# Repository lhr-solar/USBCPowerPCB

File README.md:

# USBCPowerPCB
Author: Ishan Deshpande

The purpose of this board is to be able to use a USB Type-C laptop charger to run one LV system (such as BPS or Controls). The dongle will act as a breakout; negotiating the power delivery at a fixed voltage with the laptop charger and delivering as much current as needed at a stable voltage of 12V/5V.

Currently under active development. Please reference the [USB-C PD Dongle Design Document](https://cloud.wikis.utexas.edu/wiki/spaces/LHRSOLAR/pages/28287742/2024+-+2026+USB-C+PD+Dongle+Design+Document) for more information.

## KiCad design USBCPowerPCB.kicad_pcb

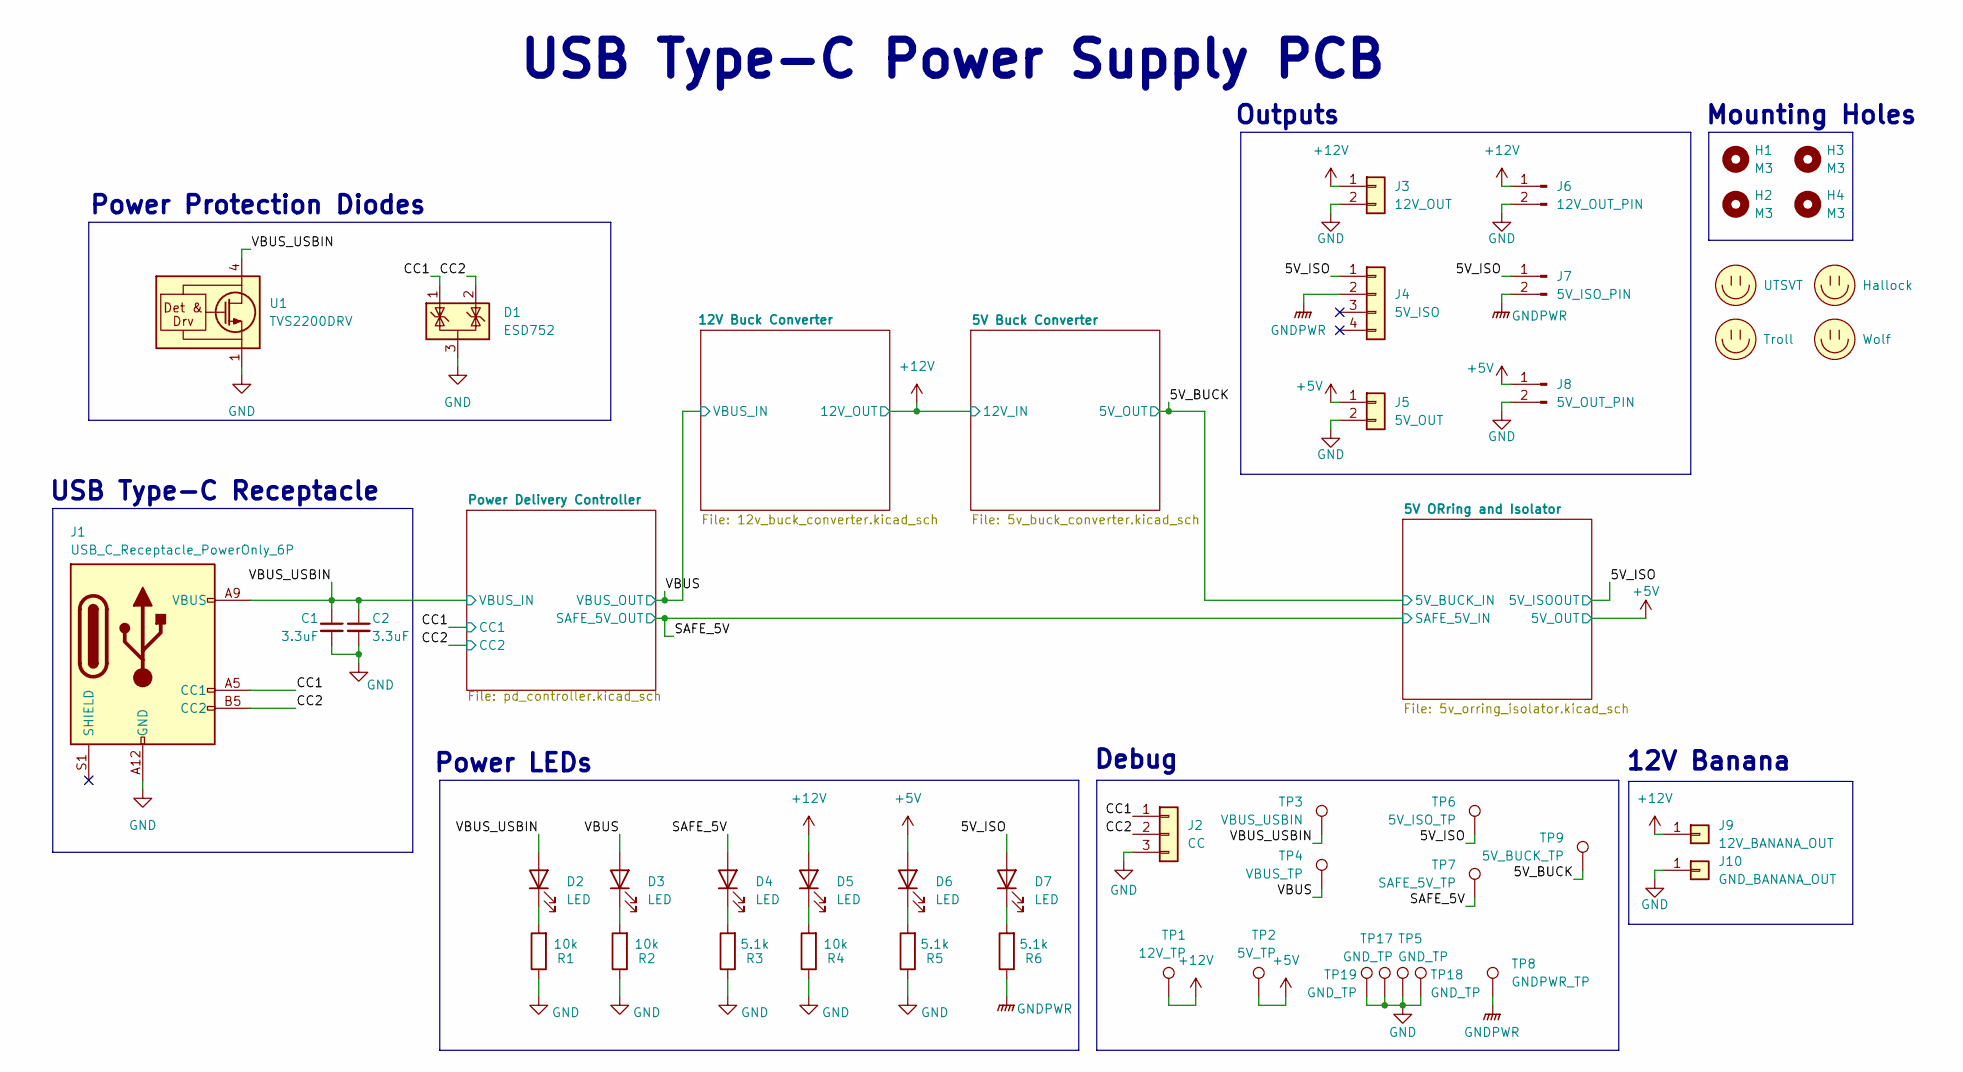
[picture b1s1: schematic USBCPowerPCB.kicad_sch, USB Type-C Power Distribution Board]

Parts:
C1, C2: 3.3uF; C_0805_2012Metric
D1: ESD752; SOT-23; Mouser Part Number ESD752DBZR
D2, D3, D4, D5, D6, D7: LED; LED_0805_2012Metric
H1, H2, H3, H4: M3; MountingHole_3.2mm_M3
J1: USB_C_Receptacle_PowerOnly_6P; TYPEC31M17
J2: CC; PinHeader_1x03_P2.54mm_Vertical
J3: 12V_OUT; Molex_MicroFit3.0_1x2xP3.00mm_PolarizingPeg_Vertical
J4: 5V_ISO; Molex_MicroFit3.0_1x4xP3.00mm_PolarizingPeg_Vertical
J5: 5V_OUT; Molex_MicroFit3.0_1x2xP3.00mm_PolarizingPeg_Vertical
J6: 12V_OUT_PIN; PinHeader_1x02_P2.54mm_Vertical
J7: 5V_ISO_PIN; PinHeader_1x02_P2.54mm_Vertical
J8: 5V_OUT_PIN; PinHeader_1x02_P2.54mm_Vertical
J9: 12V_BANANA_OUT; Banana_Jack_Horizontal
J10: GND_BANANA_OUT; Banana_Jack_Horizontal
LOGO1: UTSVT; UTSVT_Logo_Symbol
LOGO2: Hallock; Hallock_Image_Tiny
LOGO3: Troll; troll
LOGO4: Wolf; wolf_front
R1, R2, R4: 10k; R_0805_2012Metric
R3, R5, R6: 5.1k; R_0805_2012Metric
TP1: 12V_TP; TestPoint_Plated_Hole_D2.0mm
TP2: 5V_TP; TestPoint_Plated_Hole_D2.0mm
TP3: VBUS_USBIN; TestPoint_Plated_Hole_D2.0mm
TP4: VBUS_TP; TestPoint_Plated_Hole_D2.0mm
TP5, TP17, TP18: GND_TP; TestPoint_THTPad_1.0x1.0mm_Drill0.5mm
TP6: 5V_ISO_TP; TestPoint_Plated_Hole_D2.0mm
TP7: SAFE_5V_TP; TestPoint_Plated_Hole_D2.0mm
TP8: GNDPWR_TP; TestPoint_Plated_Hole_D2.0mm
TP9: 5V_BUCK_TP; TestPoint_Plated_Hole_D2.0mm
TP19: GND_TP; TestPoint_Plated_Hole_D2.0mm
U1: TVS2200DRV; WSON-6-1EP_2x2mm_P0.65mm_EP1x1.6mm

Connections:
+5V: D6.2 (A), J5.1, J8.1, TP2.1; also elsewhere on the board
+12V: D5.2 (A), J3.1, J6.1, J9.1, TP1.1; also elsewhere on the board
/5V_BUCK: TP9.1; also elsewhere on the board
/5V_ISO: D7.2 (A), J4.1, J7.1, TP6.1; also elsewhere on the board
/CC1: D1.1 (K), J1.A5 (CC1), J2.1; also elsewhere on the board
/CC2: D1.2 (K), J1.B5 (CC2), J2.2; also elsewhere on the board
/SAFE_5V: D4.2 (A), TP7.1; also elsewhere on the board
/VBUS: D3.2 (A), TP4.1; also elsewhere on the board
/VBUS_USBIN: C1.1, C2.1, D2.2 (A), J1.A4 (VBUS), J1.A9 (VBUS), J1.B9 (VBUS), TP3.1, U1.4 (IN), U1.5 (IN), U1.6 (IN); also elsewhere on the board
GND: C1.2, C2.2, D1.3 (A), J1.A1 (GND), J1.A12 (GND), J1.B12 (GND), J2.3, J3.2, J5.2, J6.2, J8.2, J10.1, R1.1, R2.1, R3.1, R4.1, R5.1, TP5.1, TP17.1, TP18.1, TP19.1, U1.1 (GND), U1.2 (GND), U1.3 (GND), U1.7 (GND); also elsewhere on the board
GNDPWR: J4.2, J7.2, R6.1, TP8.1; also elsewhere on the board
unnamed: D2.1 (K), R1.2
unnamed: D3.1 (K), R2.2
unnamed: D4.1 (K), R3.2
unnamed: D5.1 (K), R4.2
unnamed: D6.1 (K), R5.2
unnamed: D7.1 (K), R6.2

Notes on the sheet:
Outputs
Mounting Holes
Debug
Power LEDs
USB Type-C Power Supply PCB
USB Type-C Receptacle
12V Banana
Power Protection Diodes

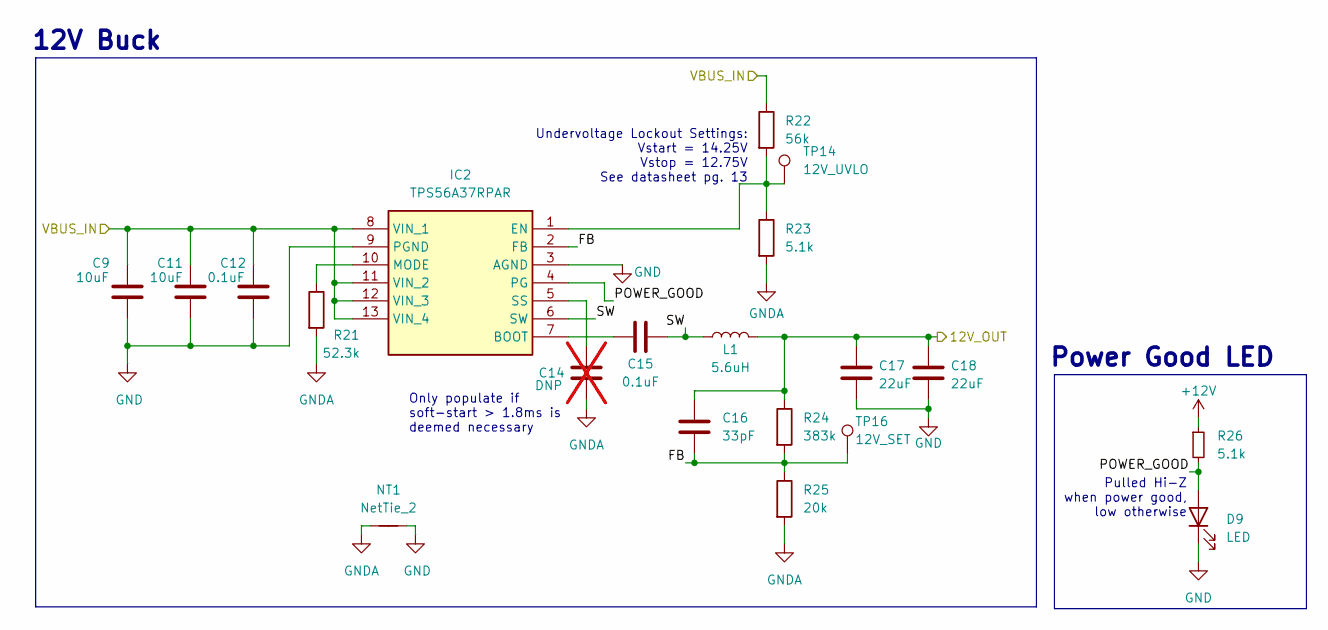
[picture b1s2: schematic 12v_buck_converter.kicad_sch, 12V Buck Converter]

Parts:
C9, C11: 10uF; C_0805_2012Metric; Mouser Part Number GRM21BR61H106KE43L
C12, C15: 0.1uF; C_0805_2012Metric; Mouser Part Number C0805C104M5RACTU
C14: DNP; C_0805_2012Metric; not fitted
C16: 33pF; C_0805_2012Metric; Mouser Part Number C0805C330K5RACTU
C17, C18: 22uF; C_0805_2012Metric; Mouser Part Number C2012X5R1V226M125AC
D9: LED; LED_0805_2012Metric; Mouser Part Number 604-APTD2012LCGCK
IC2: TPS56A37RPAR; Mouser Part Number 595-TPS56A37RPAR
L1: 5.6uH; L_Bourns_SRP1038C_10.0x10.0mm; Mouser Part Number SRP1038CC-5R6M
NT1: NetTie_2; NetTie-2_SMD_Pad2.0mm
R21: 52.3k; R_0805_2012Metric; Mouser Part Number CRCW080552K3FKEAC
R22: 56k; R_0805_2012Metric; Mouser Part Number CRCW080556K0FKEAC
R23, R26: 5.1k; R_0805_2012Metric; Mouser Part Number CRCW08055K10FKEAC
R24: 383k; R_0805_2012Metric; Mouser Part Number CRCW0805383KFKEAC
R25: 20k; R_0805_2012Metric; Mouser Part Number CRCW080520K0FKEAC
TP14: 12V_UVLO; TestPoint_THTPad_1.0x1.0mm_Drill0.5mm
TP16: 12V_SET; TestPoint_THTPad_1.0x1.0mm_Drill0.5mm

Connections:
+12V: C16.1, C17.1, C18.1, L1.2, R24.1, R26.1; also elsewhere on the board
/12V Buck Converter/FB: C16.2, IC2.2 (FB), R24.2, R25.1, TP16.1
/12V Buck Converter/POWER_GOOD: D9.2 (A), IC2.4 (PG), R26.2
/12V Buck Converter/SW: C15.2, IC2.6 (SW), L1.1
/VBUS: C9.1, C11.1, C12.1, IC2.8 (VIN_1), IC2.11 (VIN_2), IC2.12 (VIN_3), IC2.13 (VIN_4), R22.1; also elsewhere on the board
GND: C9.2, C11.2, C12.2, C17.2, C18.2, D9.1 (K), IC2.3 (AGND), IC2.9 (PGND), NT1.2; also elsewhere on the board
GNDA: C14.2, NT1.1, R21.2, R23.2, R25.2
unnamed: C15.1, IC2.7 (BOOT)
unnamed: IC2.1 (EN), R22.2, R23.1, TP14.1
unnamed: IC2.10 (MODE), R21.1
unnamed: C14.1, IC2.5 (SS)

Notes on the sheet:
Only populate if soft-start > 1.8ms is deemed necessary
Undervoltage Lockout Settings: Vstart = 14.25V Vstop = 12.75V See datasheet pg. 13
Pulled Hi-Z when power good, low otherwise
Power Good LED
12V Buck

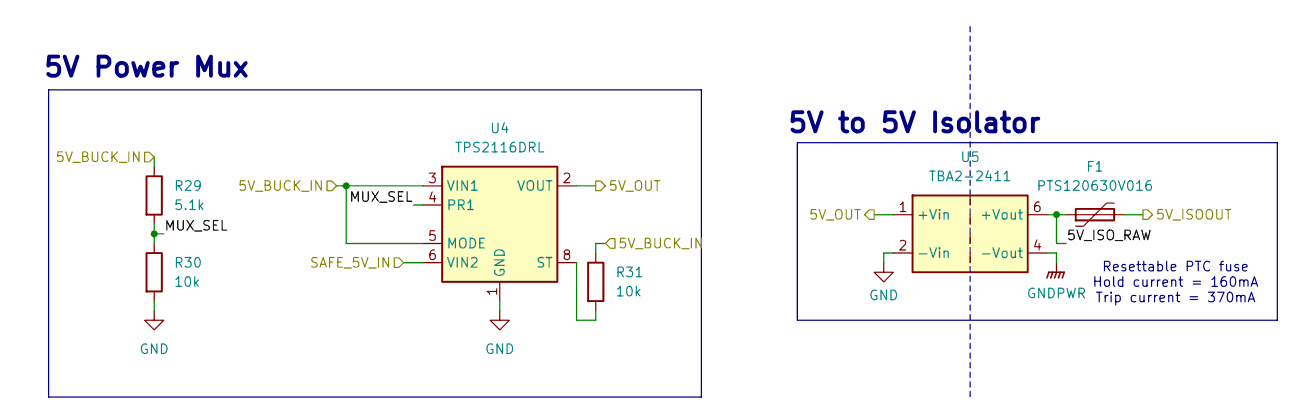
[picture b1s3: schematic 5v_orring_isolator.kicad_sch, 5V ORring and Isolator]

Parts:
F1: PTS120630V016; Fuse_1206_3216Metric
R29: 5.1k; R_0805_2012Metric
R30, R31: 10k; R_0805_2012Metric
U4: TPS2116DRL; SOT-583-8
U5: TBA2-2411; Converter_DCDC_TRACO_TBA2-xxxx_Single_THT

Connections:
+5V: U4.2 (VOUT), U4.7 (VOUT), U5.1 (+Vin); also elsewhere on the board
/5V ORring and Isolator/5V_ISO_RAW: F1.1, U5.6 (+Vout)
/5V ORring and Isolator/MUX_SEL: R29.2, R30.1, U4.4 (PR1)
/5V_BUCK: R29.1, R31.1, U4.3 (VIN1), U4.5 (MODE); also elsewhere on the board
/5V_ISO: F1.2; also elsewhere on the board
/SAFE_5V: U4.6 (VIN2); also elsewhere on the board
GND: R30.2, U4.1 (GND), U5.2 (-Vin); also elsewhere on the board
GNDPWR: U5.4 (-Vout); also elsewhere on the board
unnamed: R31.2, U4.8 (ST)

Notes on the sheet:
5V Power Mux
Resettable PTC fuse Hold current = 160mA Trip current = 370mA
5V to 5V Isolator

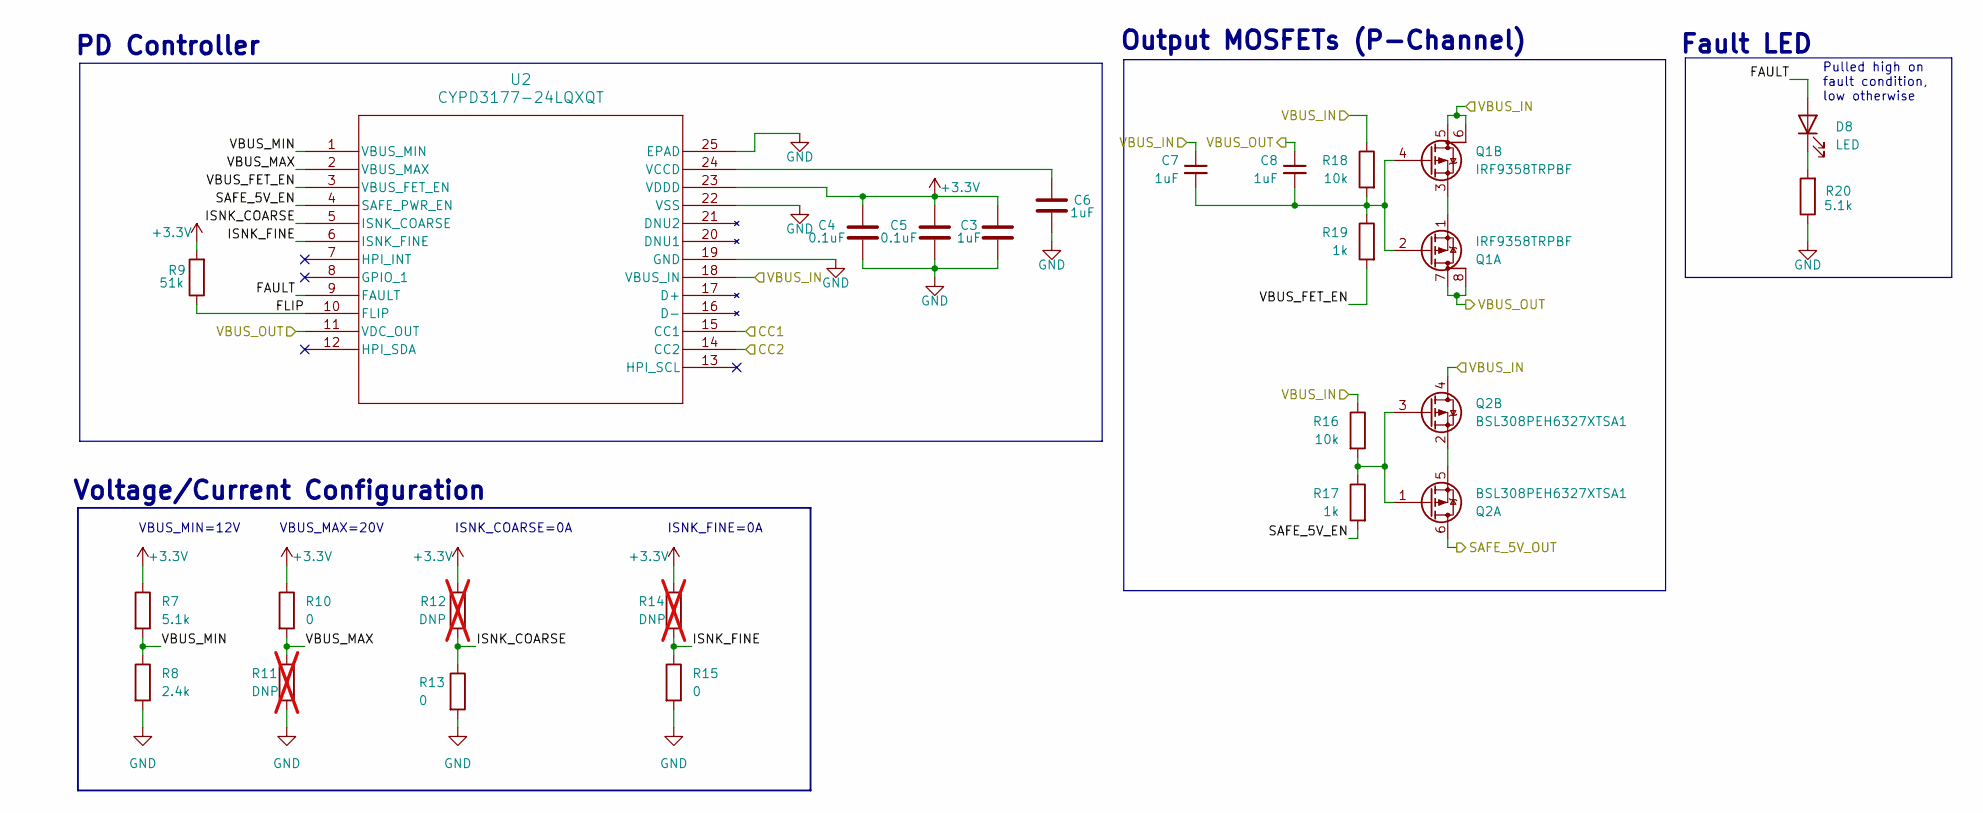
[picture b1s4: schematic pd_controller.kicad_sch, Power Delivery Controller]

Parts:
C3, C6, C7, C8: 1uF; C_0805_2012Metric; Mouser Part Number C0805C105K5PACTU
C4, C5: 0.1uF; C_0805_2012Metric; Mouser Part Number C0805C104M5RACTU
D8: LED; LED_0805_2012Metric; Mouser Part Number 604-APTD2012LCGCK
Q1: IRF9358TRPBF; SO-8_3.9x4.9mm_P1.27mm; Mouser Part Number IRF9358TRPBF
Q2: BSL308PEH6327XTSA1; SOT-23-6; Mouser Part Number BSL308PEH6327XTSA1
R7, R20: 5.1k; R_0805_2012Metric; Mouser Part Number CRCW08055K10FKEAC
R8: 2.4k; R_0805_2012Metric; Mouser Part Number CRCW08052K40FKEAC
R9: 51k; R_0805_2012Metric; Mouser Part Number CRCW080551K0FKEAC
R10, R13, R15: 0; R_0805_2012Metric
R11, R12, R14: DNP; R_0805_2012Metric; not fitted
R16, R18: 10k; R_0805_2012Metric; Mouser Part Number CRCW080510K0FKEAC
R17, R19: 1k; R_0805_2012Metric; Mouser Part Number CRCW08051K00FKEAC
U2: CYPD3177-24LQXQT; CYPD3177-24LQXQT_CYP; Mouser Part Number 727-CYPD3177-24LQXQT

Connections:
+3.3V: C3.2, C4.2, C5.2, R7.1, R9.2, R10.1, R12.1, R14.1, U2.23 (VDDD)
/CC1: U2.15 (CC1); also elsewhere on the board
/CC2: U2.14 (CC2); also elsewhere on the board
/Power Delivery Controller/FAULT: D8.2 (A), U2.9 (FAULT)
/Power Delivery Controller/FLIP: R9.1, U2.10 (FLIP)
/Power Delivery Controller/ISNK_COARSE: R12.2, R13.1, U2.5 (ISNK_COARSE)
/Power Delivery Controller/ISNK_FINE: R14.2, R15.1, U2.6 (ISNK_FINE)
/Power Delivery Controller/SAFE_5V_EN: R17.2, U2.4 (SAFE_PWR_EN)
/Power Delivery Controller/VBUS_FET_EN: R19.2, U2.3 (VBUS_FET_EN)
/Power Delivery Controller/VBUS_MAX: R10.2, R11.1, U2.2 (VBUS_MAX)
/Power Delivery Controller/VBUS_MIN: R7.2, R8.1, U2.1 (VBUS_MIN)
/SAFE_5V: Q2.6 (D); also elsewhere on the board
/VBUS: C8.1, Q1.7 (D), Q1.8 (D), U2.11 (VDC_OUT); also elsewhere on the board
/VBUS_USBIN: C7.1, Q1.5 (D), Q1.6 (D), Q2.4 (D), R16.1, R18.1, U2.18 (VBUS_IN); also elsewhere on the board
GND: C3.1, C4.1, C5.1, C6.1, R8.2, R11.2, R13.2, R15.2, R20.1, U2.19 (GND), U2.22 (VSS), U2.25 (EPAD); also elsewhere on the board
unnamed: D8.1 (K), R20.2
unnamed: C7.2, C8.2, Q1.2 (G), Q1.4 (G), R18.2, R19.1
unnamed: Q1.1 (S), Q1.3 (S)
unnamed: Q2.1 (G), Q2.3 (G), R16.2, R17.1
unnamed: Q2.2 (S), Q2.5 (S)
unnamed: C6.2, U2.24 (VCCD)

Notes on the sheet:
VBUS_MAX=20V
Fault LED
Voltage/Current Configuration
Pulled high on fault condition, low otherwise
PD Controller
ISNK_COARSE=0A
Output MOSFETs (P-Channel)
ISNK_FINE=0A
VBUS_MIN=12V

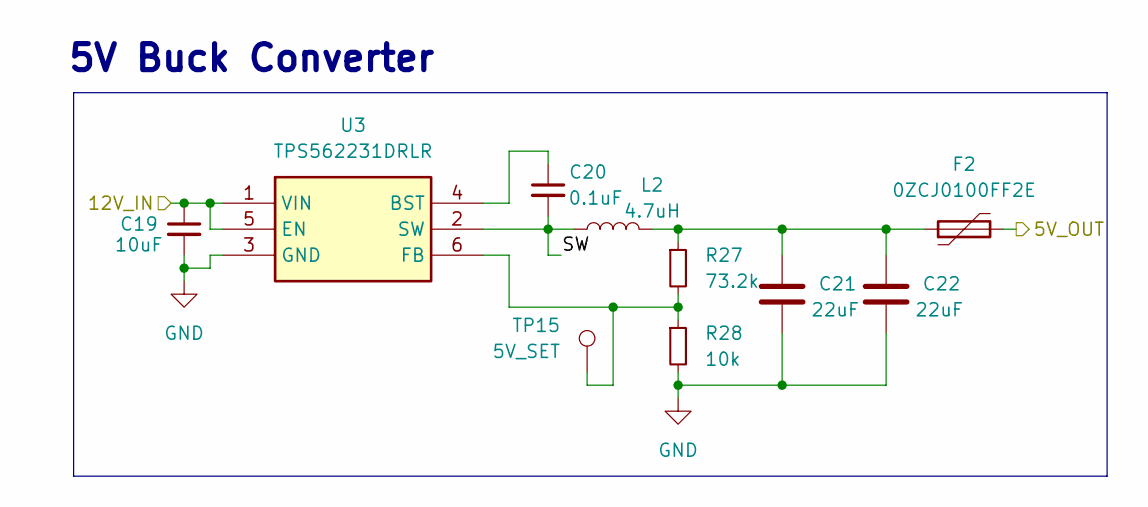
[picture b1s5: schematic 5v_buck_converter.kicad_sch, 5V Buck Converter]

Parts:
C19: 10uF; C_0805_2012Metric
C20: 0.1uF; C_0805_2012Metric
C21, C22: 22uF; C_0805_2012Metric
F2: 0ZCJ0100FF2E; Fuse_1206_3216Metric
L2: 4.7uH; INDPM5452X300N
R27: 73.2k; R_0805_2012Metric
R28: 10k; R_0805_2012Metric
TP15: 5V_SET; TestPoint_THTPad_1.0x1.0mm_Drill0.5mm
U3: TPS562231DRLR; SOT-563

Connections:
+12V: C19.1, U3.1 (VIN), U3.5 (EN); also elsewhere on the board
/5V Buck Converter/SW: C20.2, L2.1, U3.2 (SW)
/5V_BUCK: F2.2; also elsewhere on the board
GND: C19.2, C21.2, C22.2, R28.2, U3.3 (GND); also elsewhere on the board
unnamed: C21.1, C22.1, F2.1, L2.2, R27.1
unnamed: C20.1, U3.4 (BST)
unnamed: R27.2, R28.1, TP15.1, U3.6 (FB)

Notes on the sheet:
5V Buck Converter

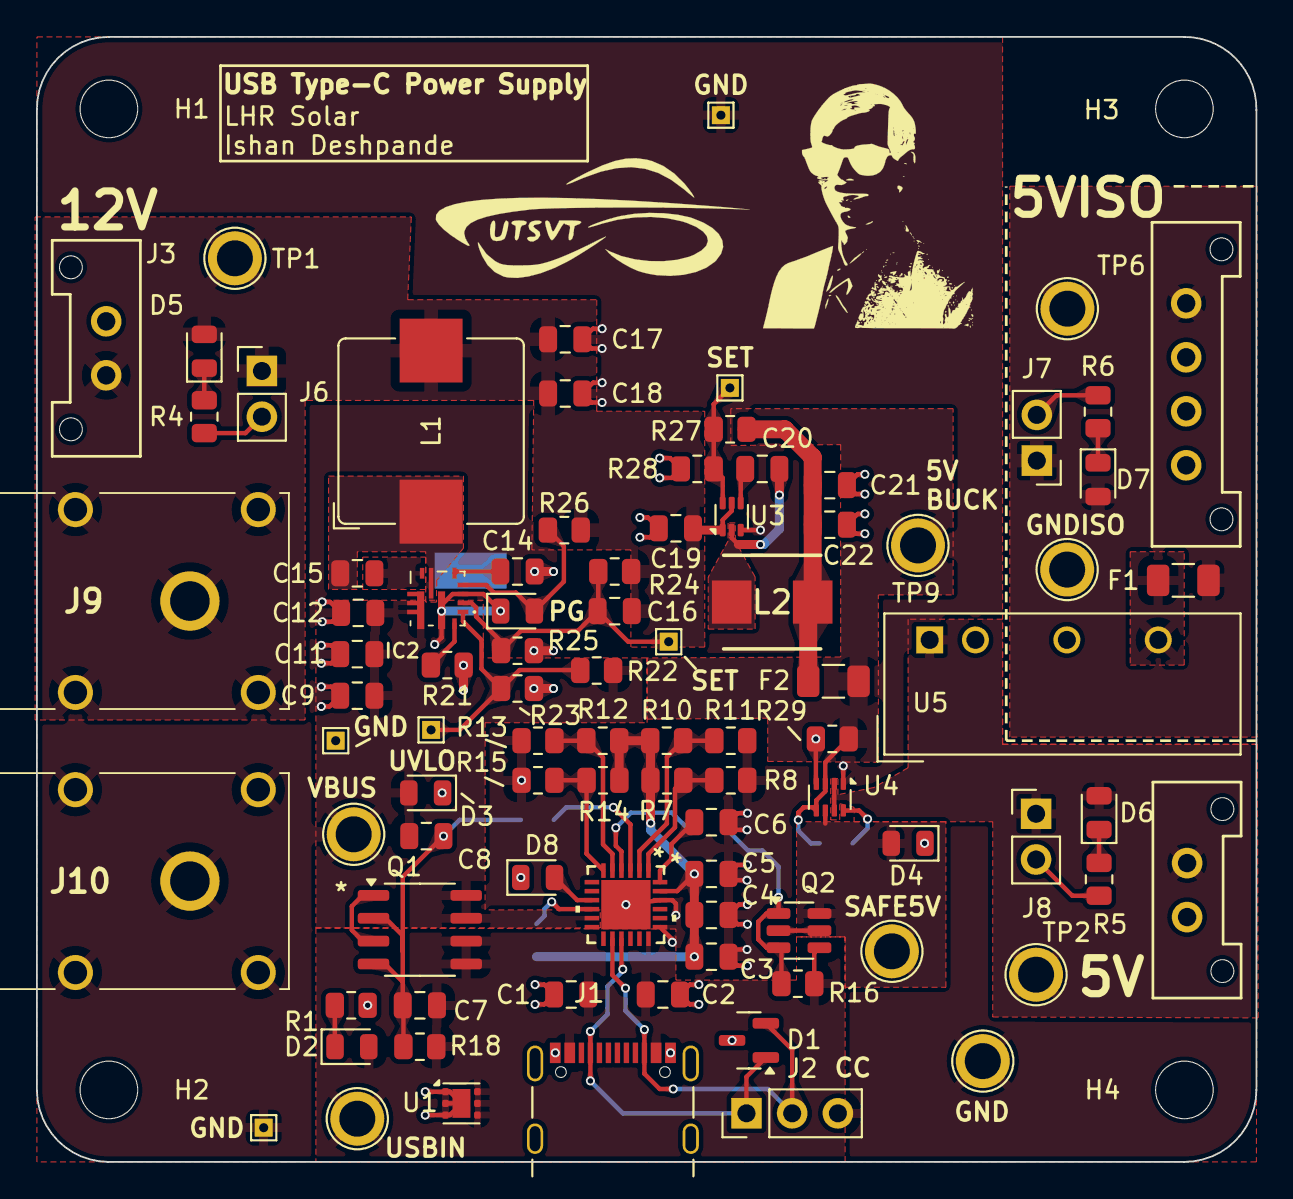
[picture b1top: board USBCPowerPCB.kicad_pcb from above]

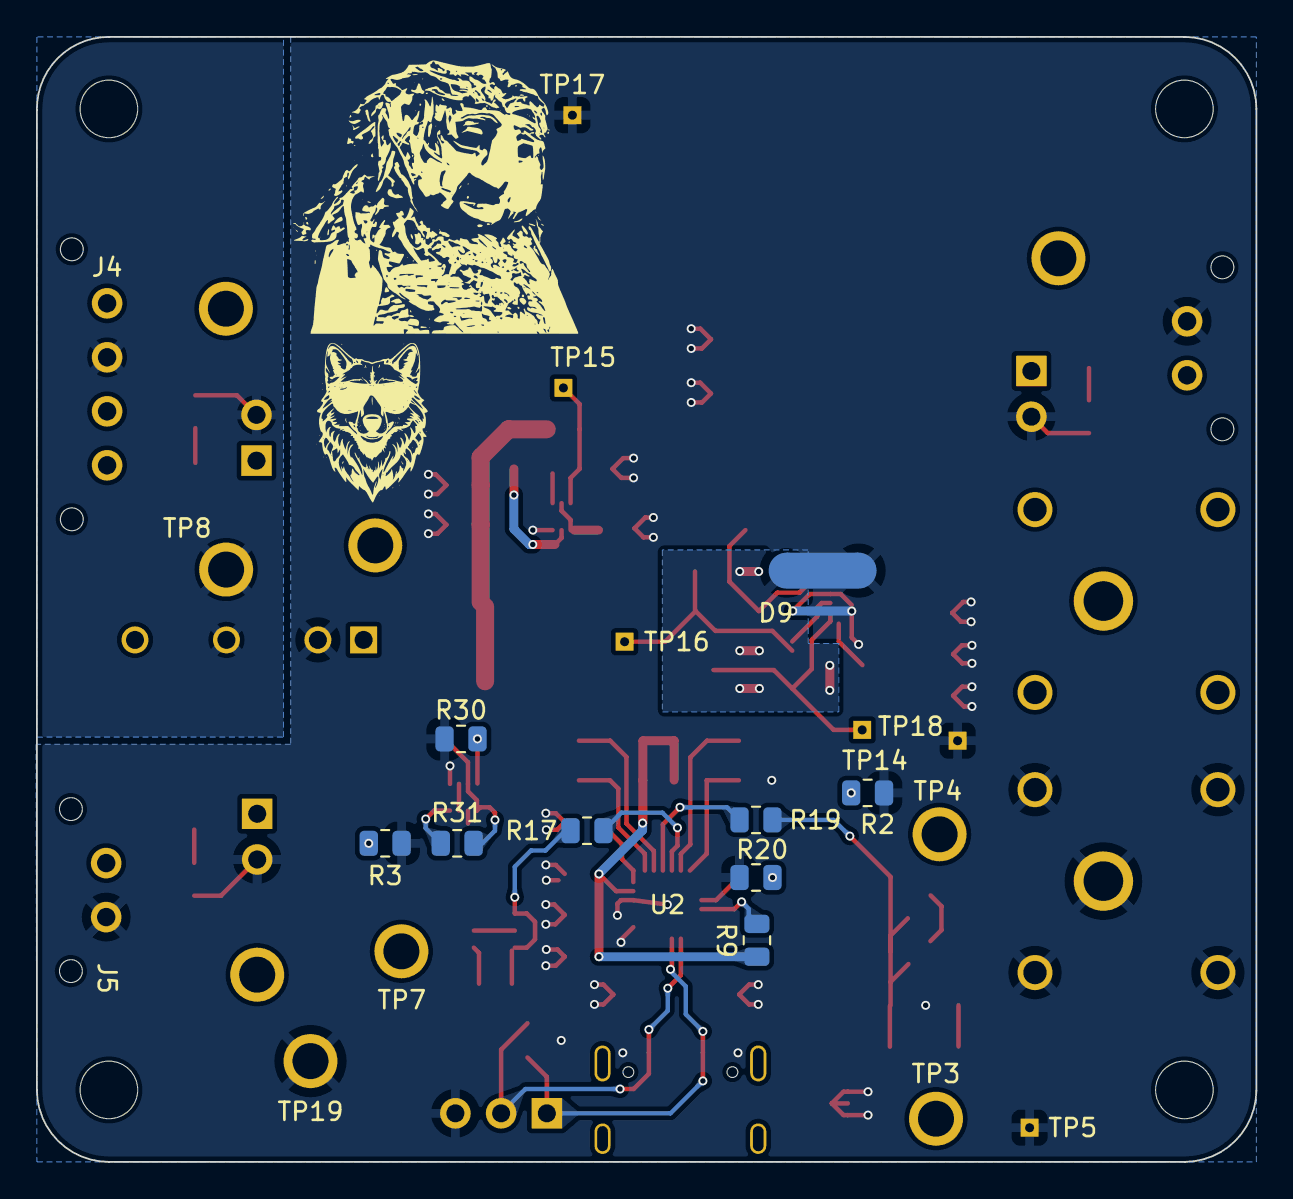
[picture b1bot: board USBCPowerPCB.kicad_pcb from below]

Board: 2 copper layers, 67.8 x 62.5 mm, 106 parts (11 on the bottom side), 47 nets.

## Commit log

2024-05-21 rename, add submodule
2024-06-02 first draft of USBC controller and 12V buck converter schematics
2024-06-02 readme
2024-06-02 added gitignore
2024-06-23 Finished 5V buck converter schematic
2024-06-23 added power good LED indicators
2024-06-23 change current protection to current monitoring
2024-07-27 moving laptops
2024-08-14 initial draft w/ current sense for 5V
2024-08-14 accidentally flipped current sense; also routed high level schematic
2024-08-14 finished first draft
2024-08-14 changed to 1-channel chip for current sense & fixed ERC
2024-08-14 added proper current limiting resistors for 2mA on seven seg
2024-08-15 updated with some new footprints (have yet to finish footprint assignment; also need to switch out inductor for 5V buck)
2024-08-29 add calcs for TPS56A37
2024-08-30 changed 5v buck to TPS56A37
2024-08-31 changed buck calcs for 5v buck
2024-08-31 almost done w/ schematic, just need to finish footprint assignment (make sure buck converter components are correctly chosen and there aren't caps that need to be different and stuff)
2024-08-31 cleaned up schematic, added power LEDs and testpoints
2024-09-01 finished footprint assignment
2024-09-01 added protection diodes
2024-09-02 changed resistor values on infineon chip output mosfets to match EZ PD BCR datasheet better
2024-09-02 removed parallel resistors
2024-09-07 address review changes, add more output protections
2024-09-07 footprint assignment again
2024-09-14 finished addressing review comments & organized bom with p/ns for everything
2024-09-14 added banana jacks for input/output to 12v buck, for isolated 12v buck testing. also filled in more part numbers for connectors.
2024-09-15 intermediate progress push before addressing Champers' and Lakshay's review comments
2024-09-16 Addressed most of the review comments, fixed power protection, added bigger caps & better part selection on 12V and 5V out, changed 5V buck inductor, fixed power good & fault LEDs
2024-09-16 Added ideal diode controller & mosfet for 12V buck power protection
2024-09-16 removed 12v output protection since buck already has OV
2024-09-18 started routing
2024-09-18 more layout updates
2024-09-19 added step files
2024-09-23 redid cypd layout, halfway through 12v buck layout
2024-09-23 big component layout moment
2024-09-23 added testpoints everywhere :)
2024-09-23 buck calcs save
2024-09-23 cleared most DRC errors, need to fix DRC warnings
2024-09-26 DRC passing: no warnings, no errors, no problem ✊🏿
2024-09-26 done
2024-10-02 made some changes to address review comments, still need to fix DRC fully and add UTSVT & Hallock silkscreen
2024-10-04 fixed clearance violations and made board 3mm shorter
2024-10-05 cleaning up stuff
2024-10-05 critical updates
2024-10-08 addressed some review comments from my 🐐 champers fu
2024-10-09 ready for review 👍🏾
2024-10-13 uncurse the cursed board
2024-10-13 addressed most of the review shit except the TVS/overcurrent protection on the 5V output
2024-10-14 added fuse to protect 5V buck converter output
2024-10-15 i am jesus christ in the flesh.
2024-10-15 i am not jesus christ...
2025-09-27 Initial Sch for USB PD IC
2025-09-27 Finished initial SCH for boost converter
